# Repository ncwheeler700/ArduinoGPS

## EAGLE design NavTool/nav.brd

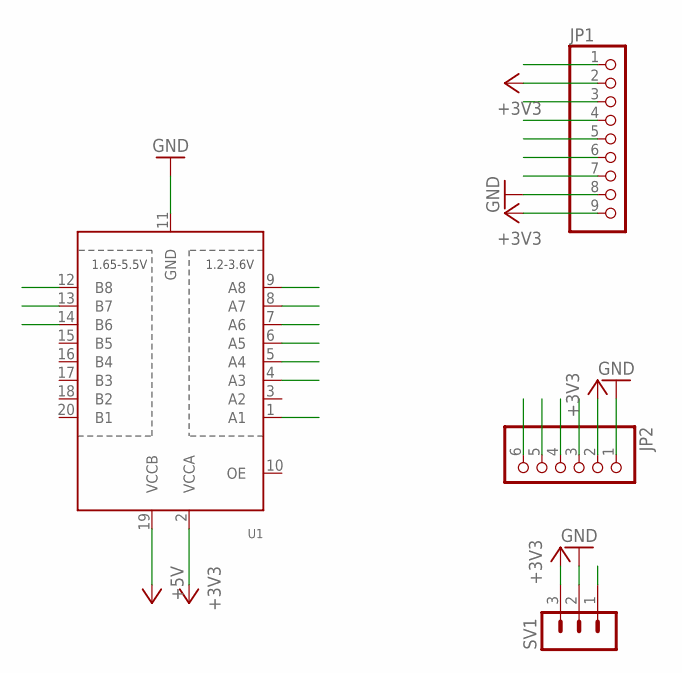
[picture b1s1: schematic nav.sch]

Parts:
JP1: PINHD-1X9; 1X09-BIG
JP2: PINHD-1X6; 1X06
SV1: MA03-1
U1: TXB0108PWR; TSSOP20

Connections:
+3V3: JP1.2, JP1.9, JP2.2, SV1.3, U1.2 (VCCA)
+5V: U1.19 (VCCB)
GND: JP1.8, JP2.1, SV1.2, U1.11 (GND)
GPS_RX: SV1.1
MISO3: JP1.1, JP2.3, U1.9 (A8)
MISO5: U1.12 (B8)
MOSI3: JP1.4, JP2.4, U1.8 (A7)
MOSI5: U1.13 (B7)
SCK3: JP1.3, JP2.5, U1.7 (A6)
SCK5: U1.14 (B6)
SCREEN_CS: JP1.7, U1.4 (A3)
SCREEN_DC: JP1.5, U1.6 (A5)
SCREEN_RESET: JP1.6, U1.5 (A4)
SD_CS: JP2.6, U1.1 (A1)

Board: 2 copper layers, 4 parts (0 on the bottom side), 9 nets, no tracks yet.

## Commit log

2017-05-21 init commit
2017-05-22 Deleted old code. Display now shows speed. Added board schematics
2017-05-22 Fixed directory structure of board files
2017-05-22 Fixed whining about eagle.epf
2017-05-23 Supports speeds greater than 10 kts
